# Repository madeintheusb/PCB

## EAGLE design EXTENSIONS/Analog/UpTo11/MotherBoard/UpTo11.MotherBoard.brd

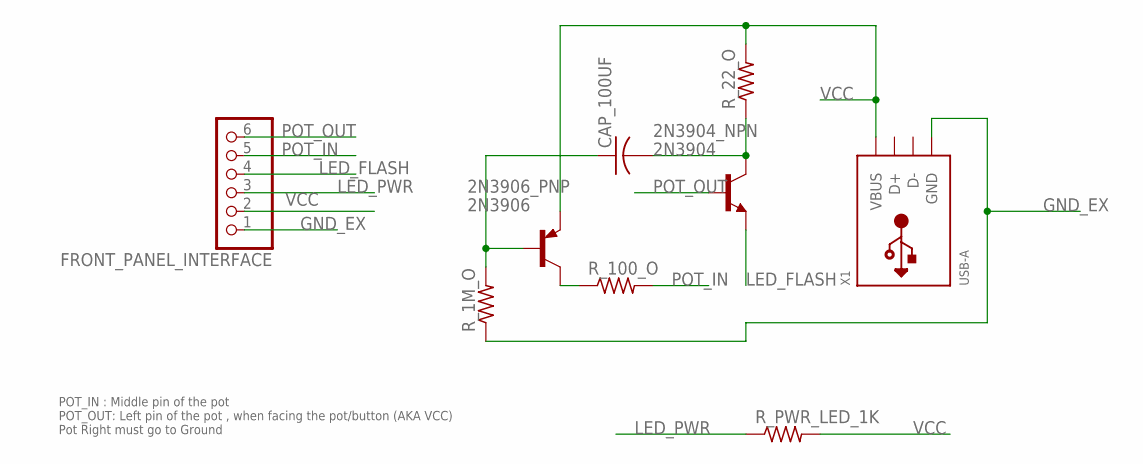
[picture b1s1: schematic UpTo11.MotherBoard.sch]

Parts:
2N3904_NPN: 2N3904; TO92
2N3906_PNP: 2N3906; TO92
CAP_100UF: C-US025-030X050; C025-030X050
FRONT_PANEL_INTERFACE: PINHD-1X6; 1X06
R_1M_O, R_22_O, R_100_O: R-US_0207/10; 0207/10
R_PWR_LED_1K: R-US_0207/10; 0207/10
X1: USB-A; MOLEX_480371000

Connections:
GND_EX: FRONT_PANEL_INTERFACE.1, R_1M_O.1, X1.4 (GND)
LED_FLASH: 2N3904_NPN.3 (E), FRONT_PANEL_INTERFACE.4
LED_PWR: FRONT_PANEL_INTERFACE.3, R_PWR_LED_1K.1
unnamed: 2N3904_NPN.1 (C), CAP_100UF.2, R_22_O.1
unnamed: 2N3906_PNP.2 (B), CAP_100UF.1, R_1M_O.2
unnamed: 2N3906_PNP.1 (C), R_100_O.1
POT_IN: FRONT_PANEL_INTERFACE.5, R_100_O.2
POT_OUT: 2N3904_NPN.2 (B), FRONT_PANEL_INTERFACE.6
VCC: 2N3906_PNP.3 (E), FRONT_PANEL_INTERFACE.2, R_22_O.2, R_PWR_LED_1K.2, X1.1 (VBUS)

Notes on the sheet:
POT_IN : Middle pin of the pot POT_OUT: Left pin of the pot , when facing the pot/button (AKA VCC) Pot Right must go to Ground

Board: 2 copper layers, 9 parts (0 on the bottom side), 9 nets, no tracks yet.

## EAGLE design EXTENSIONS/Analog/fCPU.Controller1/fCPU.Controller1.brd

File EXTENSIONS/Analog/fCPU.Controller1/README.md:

# fCPU

## Goal

Create 4 bit CPU that can
- Receive as input 2 4 bit values
- Display each value on a 7-Segment Display
- Add the 2 values
- Display the result of the addition

There is no machine code stored in some EEPROM. The program is hardcoded,
from the 10 outputs of the controller we wire each pin to execute one specific instruction.
Idealy, the program would look like this:

### Versions
- In v1 we use a controller of type 4017BE directly connected to the clock.
- In a v2 we use a SN74LS90 asprogram counter, and a SN74LS42N as the controller. The clock is connected to the program counter

| Controller Pin 	| Instruction                               	|
|----------------	|-------------------------------------------	|
| 1              	| Clear Register 1                          	|
| 2              	| Clear Register 2                          	|
| 3              	| Clear Adder output                        	|
| 4              	| Display Adder result on 7-Segment Display 	|
| 5              	| Read Register 1 from input 1              	|
| 6              	| Read Register 2 from input 2              	|
| 7              	| Add Register 1 and 2                      	|
| 8              	| Display Adder result on 7-Segment Display 	|
| 9              	| Nop                                       	|
| 10             	| Nop                                       	|

| Controller Pin 	| Instruction                               	|
|----------------	|-------------------------------------------	|
| 1              	| Clear Register 1                          	|
| 2              	| Clear Register 2                          	|
| 3              	| Nop Expected 0 + 0 = 0, is displayed          |
| 4              	| Nop                                           |
| 5              	| Nop                                           |
| 6              	| Read Register 1 from input 1, Expected Register 1 is displayed |
| 7              	| Read Register 2 from input 2  Expected Result is displayed |
| 8              	| Nop                                           |
| 9              	| Nop                                           |
|10              	| Nop                                           |

A program counter, execute instructions 1 to 10 (or the pin controller 1 to 10), in an infinite loop.

Display Limitation: 
- In v1, we can only display number from 0 to 9, we cannot display number from 10 to 15.
- No support of integer overflow when reaching number greater than 15.
    - Adder pin C4 (Carry out) could be linked to an LED.

## Architecture

Using a SN74LS90 counter, we can count from 0 to 9, to play the role of the Program Counter.

We use a SN74LS42N (Demultiplexers 4 to 10 BCD), to easily trigger up to 10 actions/instructions. Combined with a 2 inverter SN74LS14 (6 inverter/IC), for each instructions we get a pin high (CTRL_ON_X) and a pin low (CTRL_OFF_X) when in execution mode.

### Code execution
    (1) : Clear Register 1
        - CTRL_ON_1 [NC], - CTRL_OFF_1 --> REGISTER_1_CLR
        The CLR pin from the register is active low and will be reset to 0 when the wire change from state 1 to 0 and then back 1. 
        The state of the pin CTRL_OFF_1 is always high except when instruction is executed where the pin become low, clearing the register.

    (2) : Clear Register 2
        - CTRL_ON_2 [NC], - CTRL_OFF_2 --> REGISTER_2_CLR
        The CLR pin from the register is active low and will be reset to 0 when the wire change from state 1 to 0 and then back 1. 
        The state of the pin CTRL_OFF_2 is always high except when instruction is executed where the pin become low, clearing the register.

    (2) : Clear Adder
        - CTRL_ON_3, - CTRL_OFF_3

### Wiring
- CTRL_LOW_1 [NC],
- CTRL_LOW_INV_1 --> [REGISTER 1 CLR]

- CTRL_LOW_2 [NC], 
- CTRL_LOW_INV_2 --> [REGISTER 2 CLR]

- CTRL_LOW_3 [NC], 
- CTRL_LOW_INV_3 --> [REGISTER 2 CLR]

### Input device to registers
We will have 2 registers, implemented by the 2 SN74LS273 which is a 8 bit register.
Bit 1..4D are used. Bit 5..8D are tied to 0.
1 -[switch]-> resistor-to-gnd * Register 1 1D
2 -[switch]-> resistor-to-gnd * Register 1 2D
3 -[switch]-> resistor-to-gnd * Register 1 3D
4 -[switch]-> resistor-to-gnd * Register 1 4D

- EAGLE CAD Part: Package:EDG-04, Device:SW_DIP-4.
    * Pin 1,2,3,4 are are connected bit 0..3 of register
    * Pin 1,2,3,4 are also conntected to GND via a 4 resistors
        - When current does not flow pin is tied to 0
        - When current flow pin goes into register pin and also to GND via the resistor
    * Pin 5,6,7,8 are tied to VCC (1).

### Output device
- A bit bus data_bus:1,2,3,4 connected to a 7-Segment Driver, connected to one 7-Segment display
- The data bus can receive the value from register1, register2 or adder1, therefore we need 12 (3*4) diodes
    - Only register1 or register2 or adder1 can send data to the bus at one time
    - How to we activate which device set the data on the bus `TBD`

## Componenents

### Program Counter
SN74LS90
- EAGLE CAD Part: Package: KNOWN, Device:KNOWN.

### Controller v1

[4017BE](http://www.ti.com/lit/ds/symlink/cd4017b.pdf)
- CMOS
- EAGLE CAD Part: Package:DIL16, Device:CD4017
    * Check pin 8 seems to not be used in EAGLE CAD part, see Data Sheet.

### Controller/Software simulator v2

[SN74LS42N](https://www.mouser.com/ProductDetail/Texas-Instruments/SN74LS42N?qs=sGAEpiMZZMutXGli8Ay4kHCkCpxTtxgl92ZLS6s4WlY%3D)

* Demultiplexers 4 to 10 BCD
* Automatically set to 1 or execute
* Require inverting the output

- EAGLE CAD Part: Package:DIL16, Device:74LS42N, US
    * Check pin 8 seems to not be used in EAGLE CAD part, see Data Sheet.

### Inverter

[sn74ls14](http://www.ti.com/lit/ds/symlink/sn74ls14.pdf)
* CMOS
* No floating pin.
* 6 Inverter per IC

- EAGLE CAD Part: Package:DIL16, Device:74LS14N, US

### Adder
[SN74LS283N](http://www.ti.com/lit/ds/symlink/sn74ls283.pdf)
    - A Input
    - B Input
    - C0 Carry Input
    - S Ouput
    - C4 Carry Output
There is no clock or clear feature. The result is outputed all the time.

[SN7483 SN74LS83](http://www.ece.sunysb.edu/~dima/74ls83a.pdf)
    - Older version

### Register
* 8b [SN74LS273](http://www.ti.com/lit/ds/symlink/sn74ls273.pdf)
    - Experiment with a SN74LS273
    - Easier to program than the 4 bit below. We will 2 use 8b register and ignore bit 5..8.
    - About $0.25 on AliExpress
    - Programming
        * Input 1D, 2D, 3D, 4D, 5D, 6D, 7D, 8D
        * Output 1Q, 2Q, 3Q, 4Q, 5Q, 6Q, 7Q, 8Q
        * Setting value CLK 0 to 1
        * Clear to 0 CLR 1 to 0
    
* 4b [SN74LS173](http://www.ti.com/lit/ds/symlink/sn74ls173a.pdf)
    - Input 1D, 2D, 3D, 4D
    - Output 1Q,2Q, 3Q, 4Q
    - Setting input set G1=0, G2=0, CLK 0 to 1
    - Setting output M=0, N=0 (this could be set to 0 all the time to output the result)

Gated enable inputs are provided on these devices for controlling the entry of data into the flip-flops. When both data-enable (G1, G2) inputs are low, data at the D inputs are loaded into their respective flip-flops on the next positive transition of the buffered clock input. Gate output-control (M, N) inputs also are provided. When both are low, the normal logic states (high or low levels) of the four outputs are available for driving the loads or bus lines. The outputs are disabled independently from the level of the clock by a high logic level at either output-control input. The outputs then present a high impedance and neither load nor drive the bus line. Detailed operation is given in the function t

### 7 Segment Driver
- SN74LS47 common annode

### Schottky Diode 
Registers and adder data bus output is linked to the main DTA_BUS, each for bit is protected
with a Shotcky Diode (2 registers + 1 adder) * 4 = 12 diodes
- Diode 1N5817
- EAGLE CAD Parts:
    * Package Thru-Hole Package:DO35Z10, Device:1N821
    * Diode 1N5817 package:(SS12, small package)
        - Package:MELF-MLL41, Device:DIODE-MELF-MLL41 (DIODE-)

### Connector of write with different name
To connect a wire like CTRL_OFF_1 to REGISTER_1_CLR and keep different name
I use a extra connected which I will to manually solder each part.
- EAGLE CAD Parts:
    * Package SOLDERJUMPER_REFLOW, Device:SOLDERJUMPERREFLOW (SOLDERJUMPER)

### Input Device
    - pin 1..4 are bit 0 to bit 3
    - pin 1..4 are connected to register x
    - When pin 1..4 are off, they cannot be floating therefore we need to tied them to gnd
        but pin 1..4 are on, the register can handle 5v, but not gnd so we need a to go to gnd with a 
        resistor. we can use a resitor array
    - pin 5,6,7,8 are tied tied VCC for a 1
- EAGLE CAD Parts:
    * Package EDG-04, Device:SW_DIP-4

### 8 Resitor array
- EAGLE CAD Parts:
    * Package SIP10, Device:4610X

### Switch Manual Button
- Wiring
    1 -> VCC
    4 -> PIN + RESISTOR and GND
- EAGLE CAD Parts:
    * Package B3F-10XX, Device:10-XX
### LED 1206
- EAGLE CAD Parts:
    Device: LEDSMT1206 (LED) Package:1206, Library:adafruit

## Reference

### IC Series

- [7400 Series](https://en.wikipedia.org/wiki/List_of_7400-series_integrated_circuits) 

## Path

C:\DVT\MadeInTheUSB.PCB\EXTENSIONS\Analog\fCPU
## Github

https://github.com/madeintheusb/PCB/tree/master/EXTENSIONS/Analog/fCPU
https://bit.ly/2LOkVFg

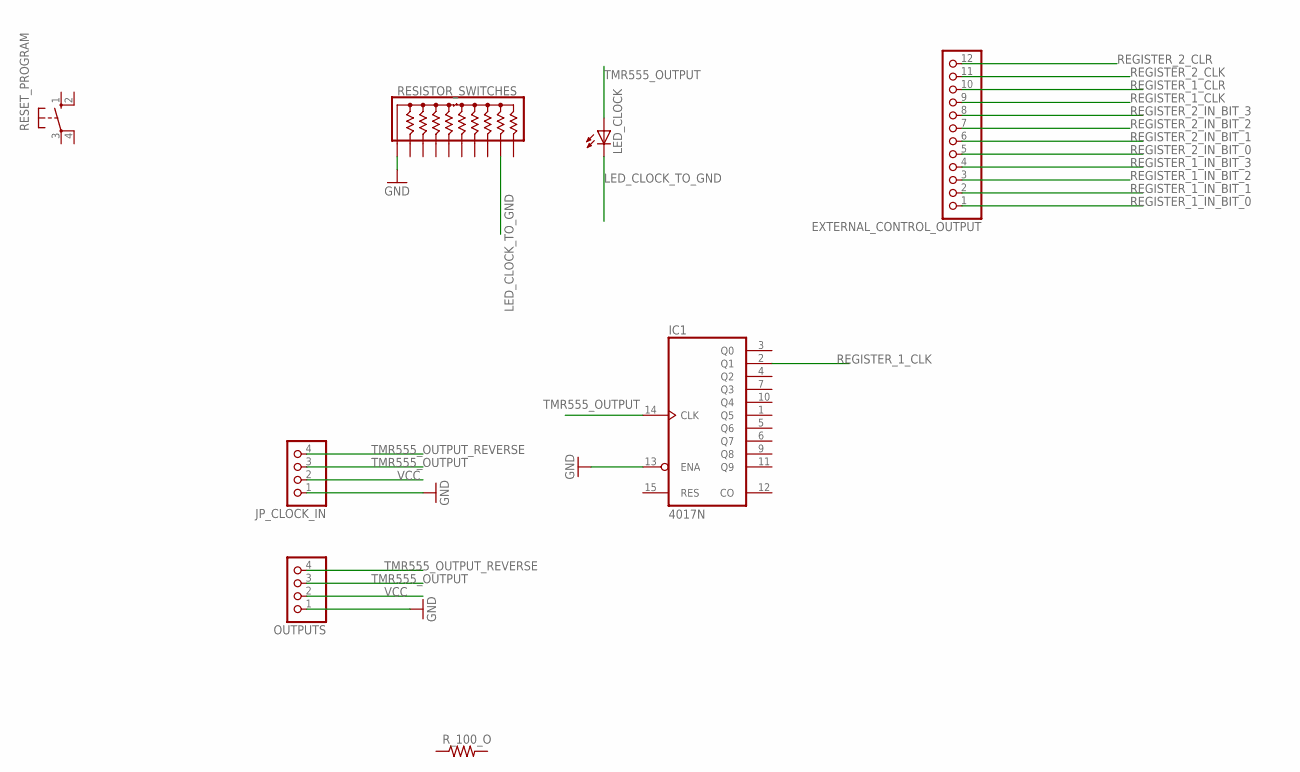
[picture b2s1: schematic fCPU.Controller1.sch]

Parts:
EXTERNAL_CONTROL_OUTPUT: PINHD-1X12; 1X12
IC1: 4017N; DIL16
JP_CLOCK_IN: PINHD-1X4; 1X04
LED_CLOCK: LEDSMT1206; 1206
OUTPUTS: PINHD-1X4; 1X04
RESET_PROGRAM: 10-XX; B3F-10XX
RESISTOR_SWITCHES: 4610X; SIP10
R_100_O: R-US_R1206; R1206

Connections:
GND: IC1.13 (ENA), JP_CLOCK_IN.1, OUTPUTS.1, RESISTOR_SWITCHES.1
LED_CLOCK_TO_GND: LED_CLOCK.C, RESISTOR_SWITCHES.9
REGISTER_1_CLK: EXTERNAL_CONTROL_OUTPUT.9, IC1.2 (Q1)
REGISTER_1_CLR: EXTERNAL_CONTROL_OUTPUT.10
REGISTER_1_IN_BIT_0: EXTERNAL_CONTROL_OUTPUT.1
REGISTER_1_IN_BIT_1: EXTERNAL_CONTROL_OUTPUT.2
REGISTER_1_IN_BIT_2: EXTERNAL_CONTROL_OUTPUT.3
REGISTER_1_IN_BIT_3: EXTERNAL_CONTROL_OUTPUT.4
REGISTER_2_CLK: EXTERNAL_CONTROL_OUTPUT.11
REGISTER_2_CLR: EXTERNAL_CONTROL_OUTPUT.12
REGISTER_2_IN_BIT_0: EXTERNAL_CONTROL_OUTPUT.5
REGISTER_2_IN_BIT_1: EXTERNAL_CONTROL_OUTPUT.6
REGISTER_2_IN_BIT_2: EXTERNAL_CONTROL_OUTPUT.7
REGISTER_2_IN_BIT_3: EXTERNAL_CONTROL_OUTPUT.8
TMR555_OUTPUT: IC1.14 (CLK), JP_CLOCK_IN.3, LED_CLOCK.A, OUTPUTS.3
TMR555_OUTPUT_REVERSE: JP_CLOCK_IN.4, OUTPUTS.4
VCC: JP_CLOCK_IN.2, OUTPUTS.2
VDD: IC1.16 (VDD)
VSS: IC1.8 (VSS)

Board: 2 copper layers, 8 parts (0 on the bottom side), 6 nets, no tracks yet.

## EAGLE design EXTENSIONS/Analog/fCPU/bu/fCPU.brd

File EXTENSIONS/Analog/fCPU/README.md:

# fCPU

## Goal

Create 4 bit CPU that can
- Receive as input 2 4 bit values
- Display each value on a 7-Segment Display
- Add the 2 values
- Display the result of the addition

In a first version, there will be no machine code stored in some EEPROM. Rather the program is hardcoded,
from the 10 outputs of the controller. Each controller's pin execute one specific instruction.
Idealy, the program would look like this:

### Versions
- In v1.1 I will use 4017BE chip as controller, directly connected to the clock.
- In a v1.2 I use a SN74LS90 chip a sprogram counter, and a SN74LS42N as the controller. The clock is connected to the program counter.

| Controller Pin 	| Instruction                               	|
|----------------	|-------------------------------------------	|
| 1              	| Clear Register 1 ~ Value is set to 0          |
| 2              	| Clear Register 2 ~ Value is set to 0          |
| Automatic         | Result displayed on 7-Segment (0)	|
| 3              	| Clock register 1, Set register 1 with value from input 1 (3)|
| Automatic         | Result displayed on 7-Segment (3)	|
| 4              	| Clear Register 1 ~ value is 0                 |
| Automatic         | Result displayed on 7-Segment (0)	|
| 5              	| Clock register 2, Set register 2 with value from input 2 (2)|
| Automatic         | Result displayed on 7-Segment (2)	|
| 6              	| Clear Register 2 ~ value is 0                 |
| Automatic         | Result displayed on 7-Segment (0)	|
| 7              	| Clock register 1 & 2, Set register 1 & 2 with value from input 1 & 2 (3+2==5)|
| Automatic         | Result displayed on 7-Segment (5) Addition	|
| 9              	| Nop                                       	|
| 10              	| Nop                                       	|

The program instructions  are executed from 1 to 10, in an infinite loop.
Special Reset button should inserted to reset 4017BE chip in v1.1 and SN74LS90 chip in 1.2

Display Limitation: 
- In v1, we can only display number from 0 to 9, we cannot display number from 10 to 15.
- No support of integer overflow when reaching number greater than 15.
    - Adder pin C4 (Carry out) could be linked to an LED.

## Architecture

Using a SN74LS90 counter, we can count from 0 to 9, to play the role of the Program Counter.

We use a SN74LS42N (Demultiplexers 4 to 10 BCD), to easily trigger up to 10 actions/instructions. Combined with a 2 inverter SN74LS14 (6 inverter/IC), for each instructions we get a pin high (CTRL_ON_X) and a pin low (CTRL_OFF_X) when in execution mode.

The Register is clock on HIGH, but is cleared on LOW, so we need the inverter.
The Adder does not need to be clocked

### Code execution
    (1) : Clear Register 1
        - CTRL_ON_1 [NC], - CTRL_OFF_1 --> REGISTER_1_CLR
        The CLR pin from the register is active low and will be reset to 0 when the wire change from state 1 to 0 and then back 1. 
        The state of the pin CTRL_OFF_1 is always high except when instruction is executed where the pin become low, clearing the register.

    (2) : Clear Register 2
        - CTRL_ON_2 [NC], - CTRL_OFF_2 --> REGISTER_2_CLR
        The CLR pin from the register is active low and will be reset to 0 when the wire change from state 1 to 0 and then back 1. 
        The state of the pin CTRL_OFF_2 is always high except when instruction is executed where the pin become low, clearing the register.
    
### Wiring
- CTRL_LOW_1 [NC],
- CTRL_LOW_INV_1 --> [REGISTER 1 CLR]

- CTRL_LOW_2 [NC], 
- CTRL_LOW_INV_2 --> [REGISTER 2 CLR]

### Input device to registers
We will have 2 registers, implemented by the 2 SN74LS273 which is a 8 bit register.
Bit 1..4D are used. Bit 5..8D are tied to GND.
The input device
1 -[switch]-> resistor-to-gnd * Register 1 1D
2 -[switch]-> resistor-to-gnd * Register 1 2D
3 -[switch]-> resistor-to-gnd * Register 1 3D
4 -[switch]-> resistor-to-gnd * Register 1 4D

- EAGLE CAD Part: Package:EDG-04, Device:SW_DIP-4.
    * Pin 1,2,3,4 are are connected bit 0..3 of register
    * Pin 1,2,3,4 are also conntected to GND via a 4 resistors
        - When current does not flow pin is tied to 0
        - When current flow pin goes into register pin and also to GND via the resistor
    * Pin 5,6,7,8 are tied to VCC (1).

### Output device
- The Adder 4 bit value is connected to the input of the 74LS47 and the 74LS47 is connected to the 7-segment display.
## Componenents

### Program Counter
SN74LS90
- EAGLE CAD Part: Package: KNOWN, Device:KNOWN.

### Controller v1

[4017BE](http://www.ti.com/lit/ds/symlink/cd4017b.pdf)

- EAGLE CAD Part: Package:DIL16, Device:CD4017
    * Check pin 8 seems to not be used in EAGLE CAD part, see Data Sheet.

### Controller/Software simulator v2

[SN74LS42N](https://www.mouser.com/ProductDetail/Texas-Instruments/SN74LS42N?qs=sGAEpiMZZMutXGli8Ay4kHCkCpxTtxgl92ZLS6s4WlY%3D)

* Demultiplexers 4 to 10 BCD
* Automatically set to 1 or execute
* Require inverting the output

- EAGLE CAD Part: Package:DIL16, Device:74LS42N, US
    * Check pin 8 seems to not be used in EAGLE CAD part, see Data Sheet.

### Inverter

[sn74ls14](http://www.ti.com/lit/ds/symlink/sn74ls14.pdf)
* No floating pin.
* 6 Inverter per IC

- EAGLE CAD Part: Package:DIL16, Device:74LS14N, US

### Adder
[SN74LS283N](http://www.ti.com/lit/ds/symlink/sn74ls283.pdf)
    - A Input
    - B Input
    - C0 Carry Input
    - S Ouput
    - C4 Carry Output
There is no clock or clear feature. The result is outputed all the time.

[SN7483 SN74LS83](http://www.ece.sunysb.edu/~dima/74ls83a.pdf)
    - Older version

### Register
* 8b [SN74LS273](http://www.ti.com/lit/ds/symlink/sn74ls273.pdf)
    - Experiment with a SN74LS273
    - Easier to program than the 4 bit below. We will 2 use 8b register and ignore bit 5..8.
    - About $0.25 on AliExpress
    - Programming
        * Input 1D, 2D, 3D, 4D, 5D, 6D, 7D, 8D
        * Output 1Q, 2Q, 3Q, 4Q, 5Q, 6Q, 7Q, 8Q
        * Setting value CLK 0 to 1
        * Clear to 0 CLR 1 to 0
    
* 4b [SN74LS173](http://www.ti.com/lit/ds/symlink/sn74ls173a.pdf)
    - Input 1D, 2D, 3D, 4D
    - Output 1Q,2Q, 3Q, 4Q
    - Setting input set G1=0, G2=0, CLK 0 to 1
    - Setting output M=0, N=0 (this could be set to 0 all the time to output the result)

Gated enable inputs are provided on these devices for controlling the entry of data into the flip-flops. When both data-enable (G1, G2) inputs are low, data at the D inputs are loaded into their respective flip-flops on the next positive transition of the buffered clock input. Gate output-control (M, N) inputs also are provided. When both are low, the normal logic states (high or low levels) of the four outputs are available for driving the loads or bus lines. The outputs are disabled independently from the level of the clock by a high logic level at either output-control input. The outputs then present a high impedance and neither load nor drive the bus line. Detailed operation is given in the function t

### 7 Segment Driver
- 74LS47 common annode

### Schottky Diode 
Registers and adder data bus output is linked to the main DTA_BUS, each for bit is protected
with a Shotcky Diode (2 registers + 1 adder) * 4 = 12 diodes
- Diode 1N5817
- EAGLE CAD Parts:
    * Package Thru-Hole Package:DO35Z10, Device:1N821
    * Diode 1N5817 package:(SS12, small package)
        - Package:MELF-MLL41, Device:DIODE-MELF-MLL41 (DIODE-)

### Connector of write with different name
To connect a wire like CTRL_OFF_1 to REGISTER_1_CLR and keep different name
I use a extra connected which I will to manually solder each part.
- EAGLE CAD Parts:
    * Package SOLDERJUMPER_REFLOW, Device:SOLDERJUMPERREFLOW (SOLDERJUMPER)

### Input Device
    - pin 1..4 are bit 0 to bit 3
    - pin 1..4 are connected to register x
    - When pin 1..4 are off, they cannot be floating therefore we need to tied them to gnd
        but pin 1..4 are on, the register can handle 5v, but not gnd so we need a to go to gnd with a 
        resistor. we can use a resitor array
    - pin 5,6,7,8 are tied tied VCC for a 1
- EAGLE CAD Parts:
    * Package EDG-04, Device:SW_DIP-4

### 8 Resitor array
- EAGLE CAD Parts:
    * Package SIP10, Device:4610X

### Switch Manual Button
- Wiring
    1 -> VCC
    4 -> PIN + RESISTOR and GND
- EAGLE CAD Parts:
    * Package B3F-10XX, Device:10-XX
### LED 1206
- EAGLE CAD Parts:
    Device: LEDSMT1206 (LED) Package:1206, Library:adafruit

## Reference

### IC Series

- [7400 Series](https://en.wikipedia.org/wiki/List_of_7400-series_integrated_circuits) 

## Path

C:\DVT\MadeInTheUSB.PCB\EXTENSIONS\Analog\fCPU
## Github

https://github.com/madeintheusb/PCB/tree/master/EXTENSIONS/Analog/fCPU
https://bit.ly/2LOkVFg

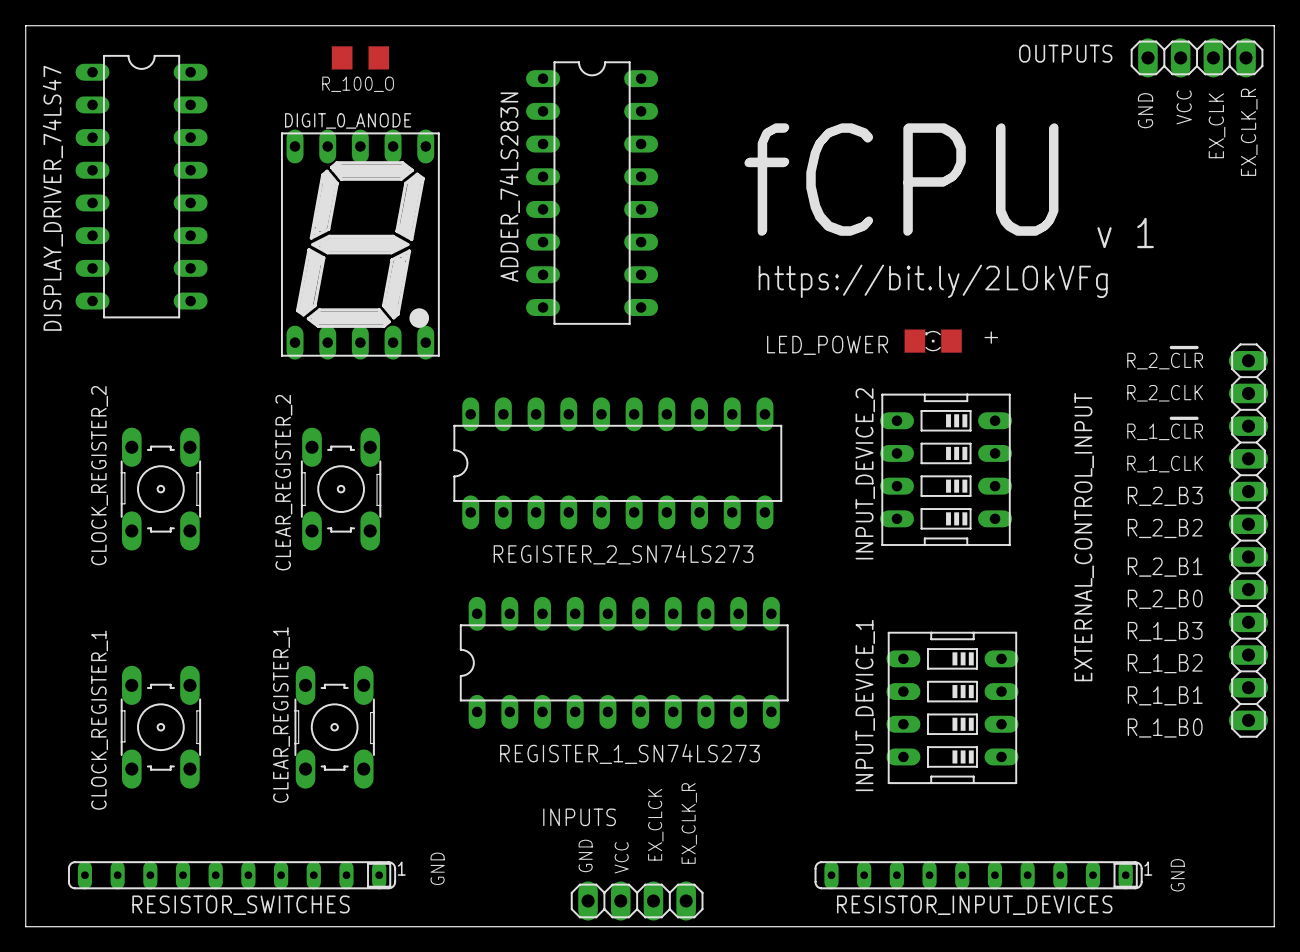
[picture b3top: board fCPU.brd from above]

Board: 2 copper layers, 97.0 x 70.0 mm, 18 parts (0 on the bottom side), 39 nets, no tracks yet.

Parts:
ADDER_74LS283N: 74LS283N; DIL16
CLEAR_REGISTER_1, CLEAR_REGISTER_2: B3F-10XX
CLOCK_REGISTER_1, CLOCK_REGISTER_2: B3F-10XX
DIGIT_0_ANODE: 7SEG-13
DISPLAY_DRIVER_74LS47: 74LS47N; DIL16
EXTERNAL_CONTROL_INPUT: 1X12
INPUT_DEVICE_1, INPUT_DEVICE_2: EDG-04
JP_CLOCK_IN: 1X04
LED_POWER: 1206
OUTPUTS: 1X04
REGISTER_1_SN74LS273, REGISTER_2_SN74LS273: 74273N; DIL20
RESISTOR_INPUT_DEVICES: SIP10
RESISTOR_SWITCHES: SIP10
R_100_O: R1206

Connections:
CLEAR_REGISTER_1_TO_GND: CLEAR_REGISTER_1.1, RESISTOR_SWITCHES.4
CLEAR_REGISTER_2_TO_GND: CLEAR_REGISTER_2.1, RESISTOR_SWITCHES.5
DTA_BUS_0: ADDER_74LS283N.4, DISPLAY_DRIVER_74LS47.7
DTA_BUS_1: ADDER_74LS283N.1, DISPLAY_DRIVER_74LS47.1
DTA_BUS_2: ADDER_74LS283N.13, DISPLAY_DRIVER_74LS47.2
DTA_BUS_3: ADDER_74LS283N.10, DISPLAY_DRIVER_74LS47.6
GND: ADDER_74LS283N.7, ADDER_74LS283N.8, DISPLAY_DRIVER_74LS47.8, JP_CLOCK_IN.1, OUTPUTS.1, REGISTER_1_SN74LS273.10, REGISTER_1_SN74LS273.13, REGISTER_1_SN74LS273.14, REGISTER_1_SN74LS273.17, REGISTER_1_SN74LS273.18, REGISTER_2_SN74LS273.10, REGISTER_2_SN74LS273.13, REGISTER_2_SN74LS273.14, REGISTER_2_SN74LS273.17, REGISTER_2_SN74LS273.18, RESISTOR_INPUT_DEVICES.1, RESISTOR_SWITCHES.1
LED_POWER_TO_GND: LED_POWER.C, RESISTOR_SWITCHES.9
unnamed: DIGIT_0_ANODE.8, R_100_O.1
REGISTER_1_CLK: CLOCK_REGISTER_1.4, EXTERNAL_CONTROL_INPUT.9, REGISTER_1_SN74LS273.11, RESISTOR_SWITCHES.2
REGISTER_1_CLR: CLEAR_REGISTER_1.4, EXTERNAL_CONTROL_INPUT.10, REGISTER_1_SN74LS273.1
REGISTER_1_IN_BIT_0: EXTERNAL_CONTROL_INPUT.1, INPUT_DEVICE_1.1, REGISTER_1_SN74LS273.3, RESISTOR_INPUT_DEVICES.2
REGISTER_1_IN_BIT_1: EXTERNAL_CONTROL_INPUT.2, INPUT_DEVICE_1.2, REGISTER_1_SN74LS273.4, RESISTOR_INPUT_DEVICES.3
REGISTER_1_IN_BIT_2: EXTERNAL_CONTROL_INPUT.3, INPUT_DEVICE_1.3, REGISTER_1_SN74LS273.7, RESISTOR_INPUT_DEVICES.4
REGISTER_1_IN_BIT_3: EXTERNAL_CONTROL_INPUT.4, INPUT_DEVICE_1.4, REGISTER_1_SN74LS273.8, RESISTOR_INPUT_DEVICES.5
REGISTER_1_OUT_BIT_0: ADDER_74LS283N.5, REGISTER_1_SN74LS273.2
REGISTER_1_OUT_BIT_1: ADDER_74LS283N.3, REGISTER_1_SN74LS273.5
REGISTER_1_OUT_BIT_2: ADDER_74LS283N.14, REGISTER_1_SN74LS273.6
REGISTER_1_OUT_BIT_3: ADDER_74LS283N.12, REGISTER_1_SN74LS273.9
REGISTER_2_CLK: CLOCK_REGISTER_2.4, EXTERNAL_CONTROL_INPUT.11, REGISTER_2_SN74LS273.11, RESISTOR_SWITCHES.3
REGISTER_2_CLR: CLEAR_REGISTER_2.4, EXTERNAL_CONTROL_INPUT.12, REGISTER_2_SN74LS273.1
REGISTER_2_IN_BIT_0: EXTERNAL_CONTROL_INPUT.5, INPUT_DEVICE_2.1, REGISTER_2_SN74LS273.3, RESISTOR_INPUT_DEVICES.6
REGISTER_2_IN_BIT_1: EXTERNAL_CONTROL_INPUT.6, INPUT_DEVICE_2.2, REGISTER_2_SN74LS273.4, RESISTOR_INPUT_DEVICES.7
REGISTER_2_IN_BIT_2: EXTERNAL_CONTROL_INPUT.7, INPUT_DEVICE_2.3, REGISTER_2_SN74LS273.7, RESISTOR_INPUT_DEVICES.8
REGISTER_2_IN_BIT_3: EXTERNAL_CONTROL_INPUT.8, INPUT_DEVICE_2.4, REGISTER_2_SN74LS273.8, RESISTOR_INPUT_DEVICES.9
REGISTER_2_OUT_BIT_0: ADDER_74LS283N.6, REGISTER_2_SN74LS273.2
REGISTER_2_OUT_BIT_1: ADDER_74LS283N.2, REGISTER_2_SN74LS273.5
REGISTER_2_OUT_BIT_2: ADDER_74LS283N.15, REGISTER_2_SN74LS273.6
REGISTER_2_OUT_BIT_3: ADDER_74LS283N.11, REGISTER_2_SN74LS273.9
SEG_1_DA: DIGIT_0_ANODE.7, DISPLAY_DRIVER_74LS47.13
SEG_1_DB: DIGIT_0_ANODE.6, DISPLAY_DRIVER_74LS47.12
SEG_1_DC: DIGIT_0_ANODE.4, DISPLAY_DRIVER_74LS47.11
SEG_1_DD: DIGIT_0_ANODE.2, DISPLAY_DRIVER_74LS47.10
SEG_1_DE: DIGIT_0_ANODE.1, DISPLAY_DRIVER_74LS47.9
SEG_1_DF: DIGIT_0_ANODE.9, DISPLAY_DRIVER_74LS47.15
SEG_1_DG: DIGIT_0_ANODE.10, DISPLAY_DRIVER_74LS47.14
TMR555_OUTPUT: JP_CLOCK_IN.3, OUTPUTS.3
TMR555_OUTPUT_REVERSE: JP_CLOCK_IN.4, OUTPUTS.4
VCC: ADDER_74LS283N.16, CLOCK_REGISTER_1.1, CLOCK_REGISTER_2.1, DISPLAY_DRIVER_74LS47.3, DISPLAY_DRIVER_74LS47.4, DISPLAY_DRIVER_74LS47.5, DISPLAY_DRIVER_74LS47.16, INPUT_DEVICE_1.5, INPUT_DEVICE_1.6, INPUT_DEVICE_1.7, INPUT_DEVICE_1.8, INPUT_DEVICE_2.5, INPUT_DEVICE_2.6, INPUT_DEVICE_2.7, INPUT_DEVICE_2.8, JP_CLOCK_IN.2, LED_POWER.A, OUTPUTS.2, REGISTER_1_SN74LS273.20, REGISTER_2_SN74LS273.20, R_100_O.2

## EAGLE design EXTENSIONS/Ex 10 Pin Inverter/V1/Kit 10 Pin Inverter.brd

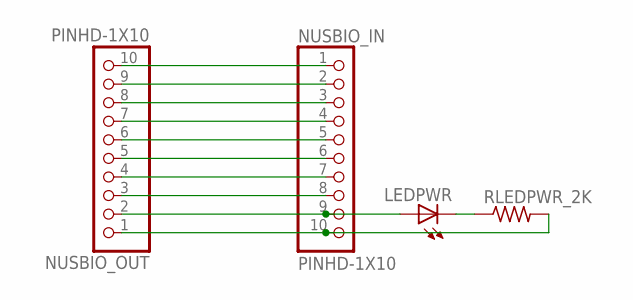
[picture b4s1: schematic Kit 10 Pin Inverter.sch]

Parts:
LEDPWR: LEDCHIPLED_0805; CHIPLED_0805
NUSBIO_IN: PINHD-1X10; 1X10-BIG
NUSBIO_OUT: PINHD-1X10; 1X10-BIG
RLEDPWR_2K: R-US_R0805; R0805

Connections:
unnamed: NUSBIO_IN.1, NUSBIO_OUT.10
unnamed: NUSBIO_IN.2, NUSBIO_OUT.9
unnamed: NUSBIO_IN.3, NUSBIO_OUT.8
unnamed: NUSBIO_IN.4, NUSBIO_OUT.7
unnamed: NUSBIO_IN.5, NUSBIO_OUT.6
unnamed: NUSBIO_IN.6, NUSBIO_OUT.5
unnamed: NUSBIO_IN.7, NUSBIO_OUT.4
unnamed: NUSBIO_IN.8, NUSBIO_OUT.3
unnamed: LEDPWR.A, NUSBIO_IN.9, NUSBIO_OUT.2
unnamed: NUSBIO_IN.10, NUSBIO_OUT.1, RLEDPWR_2K.2
unnamed: LEDPWR.C, RLEDPWR_2K.1

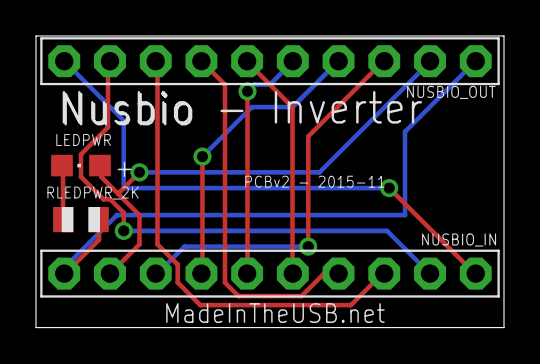
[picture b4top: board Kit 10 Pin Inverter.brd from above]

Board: 2 copper layers, 26.0 x 16.2 mm, 4 parts (0 on the bottom side), 11 nets.
